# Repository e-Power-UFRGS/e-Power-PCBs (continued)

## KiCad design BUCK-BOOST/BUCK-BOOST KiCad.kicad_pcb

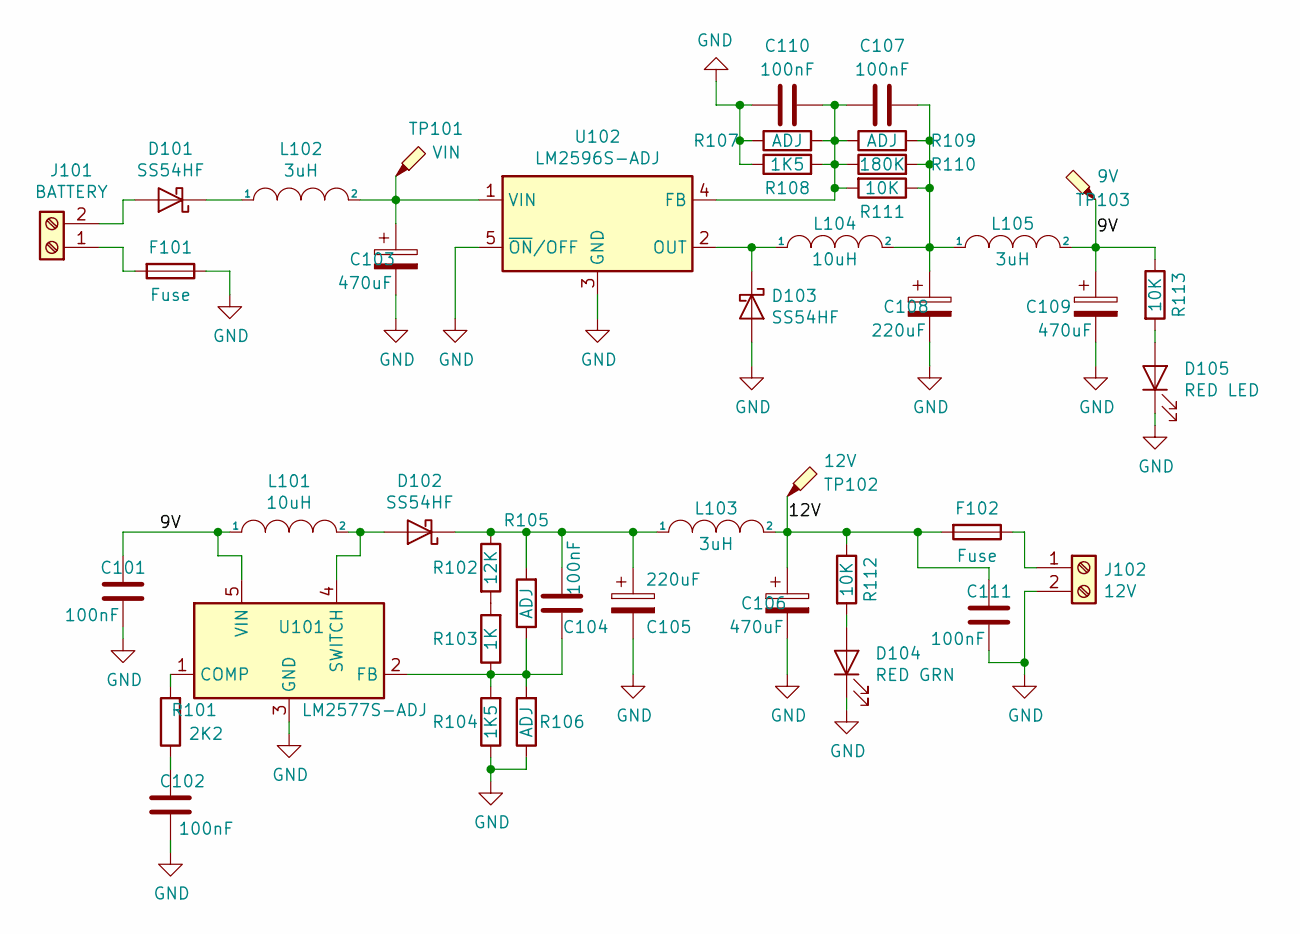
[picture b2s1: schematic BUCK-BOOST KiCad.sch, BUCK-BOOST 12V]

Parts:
C101, C102, C104, C107, C110, C111: 100nF; C_0805_2012Metric
C103, C106, C109: 470uF; CP_Elec_10x10
C105, C108: 220uF; CP_Elec_10x10
D101, D102, D103: SS54HF; DO-214AC
D104: RED GRN; LED_0805_1.15x1.40mm_HandSolder
D105: RED LED; LED_0805_1.15x1.40mm_HandSolder
F101, F102: Fuse; Fuse_SMD
J101: BATTERY; PinHeader_1x02_P2.54mm_Vertical
J102: 12V; PinHeader_1x02_P2.54mm_Vertical
L101, L104: 10uH; L_10.4x10.4_H4.8
L102, L103, L105: 3uH; L_10.4x10.4_H4.8
R101: 2K2; R_0805_2012Metric
R102: 12K; R_0805_2012Metric
R103: 1K; R_0805_2012Metric
R104, R108: 1K5; R_0805_2012Metric
R105, R106, R107, R109: ADJ; R_0805_2012Metric
R110: 180K; R_0805_2012Metric
R111, R112, R113: 10K; R_0805_2012Metric
TP101: VIN; TestPoint_Pad_1.5x1.5mm
TP102: 12V; TestPoint_Pad_1.5x1.5mm
TP103: 9V; TestPoint_Pad_1.5x1.5mm
U101: LM2577S-ADJ; TO-263-5_TabPin3
U102: LM2596S-ADJ; TO-263-5_TabPin3

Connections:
/9V: C101.2, C109.1, L101.1, L105.2, R113.1, TP103.1, U101.5 (VIN)
/12V: C106.1, C111.2, F102.2, L103.2, R112.1, TP102.1
GND: C101.1, C102.1, C103.2, C105.2, C106.2, C108.2, C109.2, C110.2, C111.1, D103.2 (A), D104.1 (K), D105.1 (K), F101.1, J102.2, R104.1, R106.1, R107.1, R108.1, U101.3 (GND), U102.3 (GND), U102.5 (~ON~/OFF)
unnamed: C102.2, R101.1
unnamed: C103.1, L102.2, TP101.1, U102.1 (VIN)
unnamed: C104.1, R103.1, R104.2, R105.1, R106.2, U101.2 (FB)
unnamed: C104.2, C105.1, D102.1 (K), L103.1, R102.1, R105.2
unnamed: C107.1, C108.1, L104.2, L105.1, R109.2, R110.2, R111.1
unnamed: C107.2, C110.1, R107.2, R108.2, R109.1, R110.1, R111.2, U102.4 (FB)
unnamed: D101.1 (K), L102.1
unnamed: D101.2 (A), J101.2
unnamed: D102.2 (A), L101.2, U101.4 (SWITCH)
unnamed: D103.1 (K), L104.1, U102.2 (OUT)
unnamed: D104.2 (A), R112.2
unnamed: D105.2 (A), R113.2
unnamed: F101.2, J101.1
unnamed: F102.1, J102.1
unnamed: R101.2, U101.1 (COMP)
unnamed: R102.2, R103.2

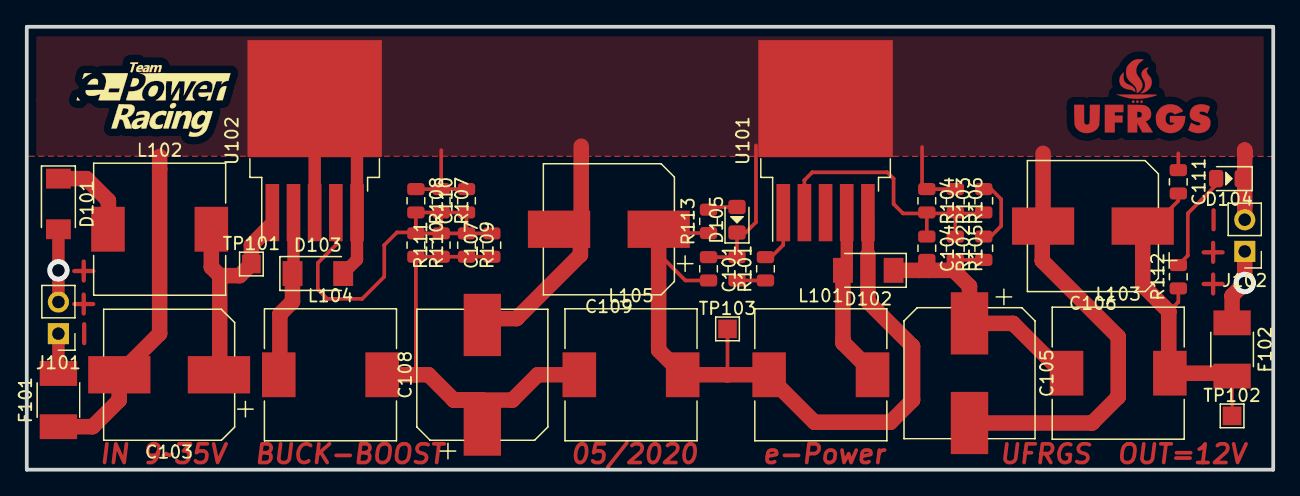
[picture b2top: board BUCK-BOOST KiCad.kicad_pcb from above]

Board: 2 copper layers, 100.1 x 35.6 mm, 43 parts (0 on the bottom side), 19 nets.

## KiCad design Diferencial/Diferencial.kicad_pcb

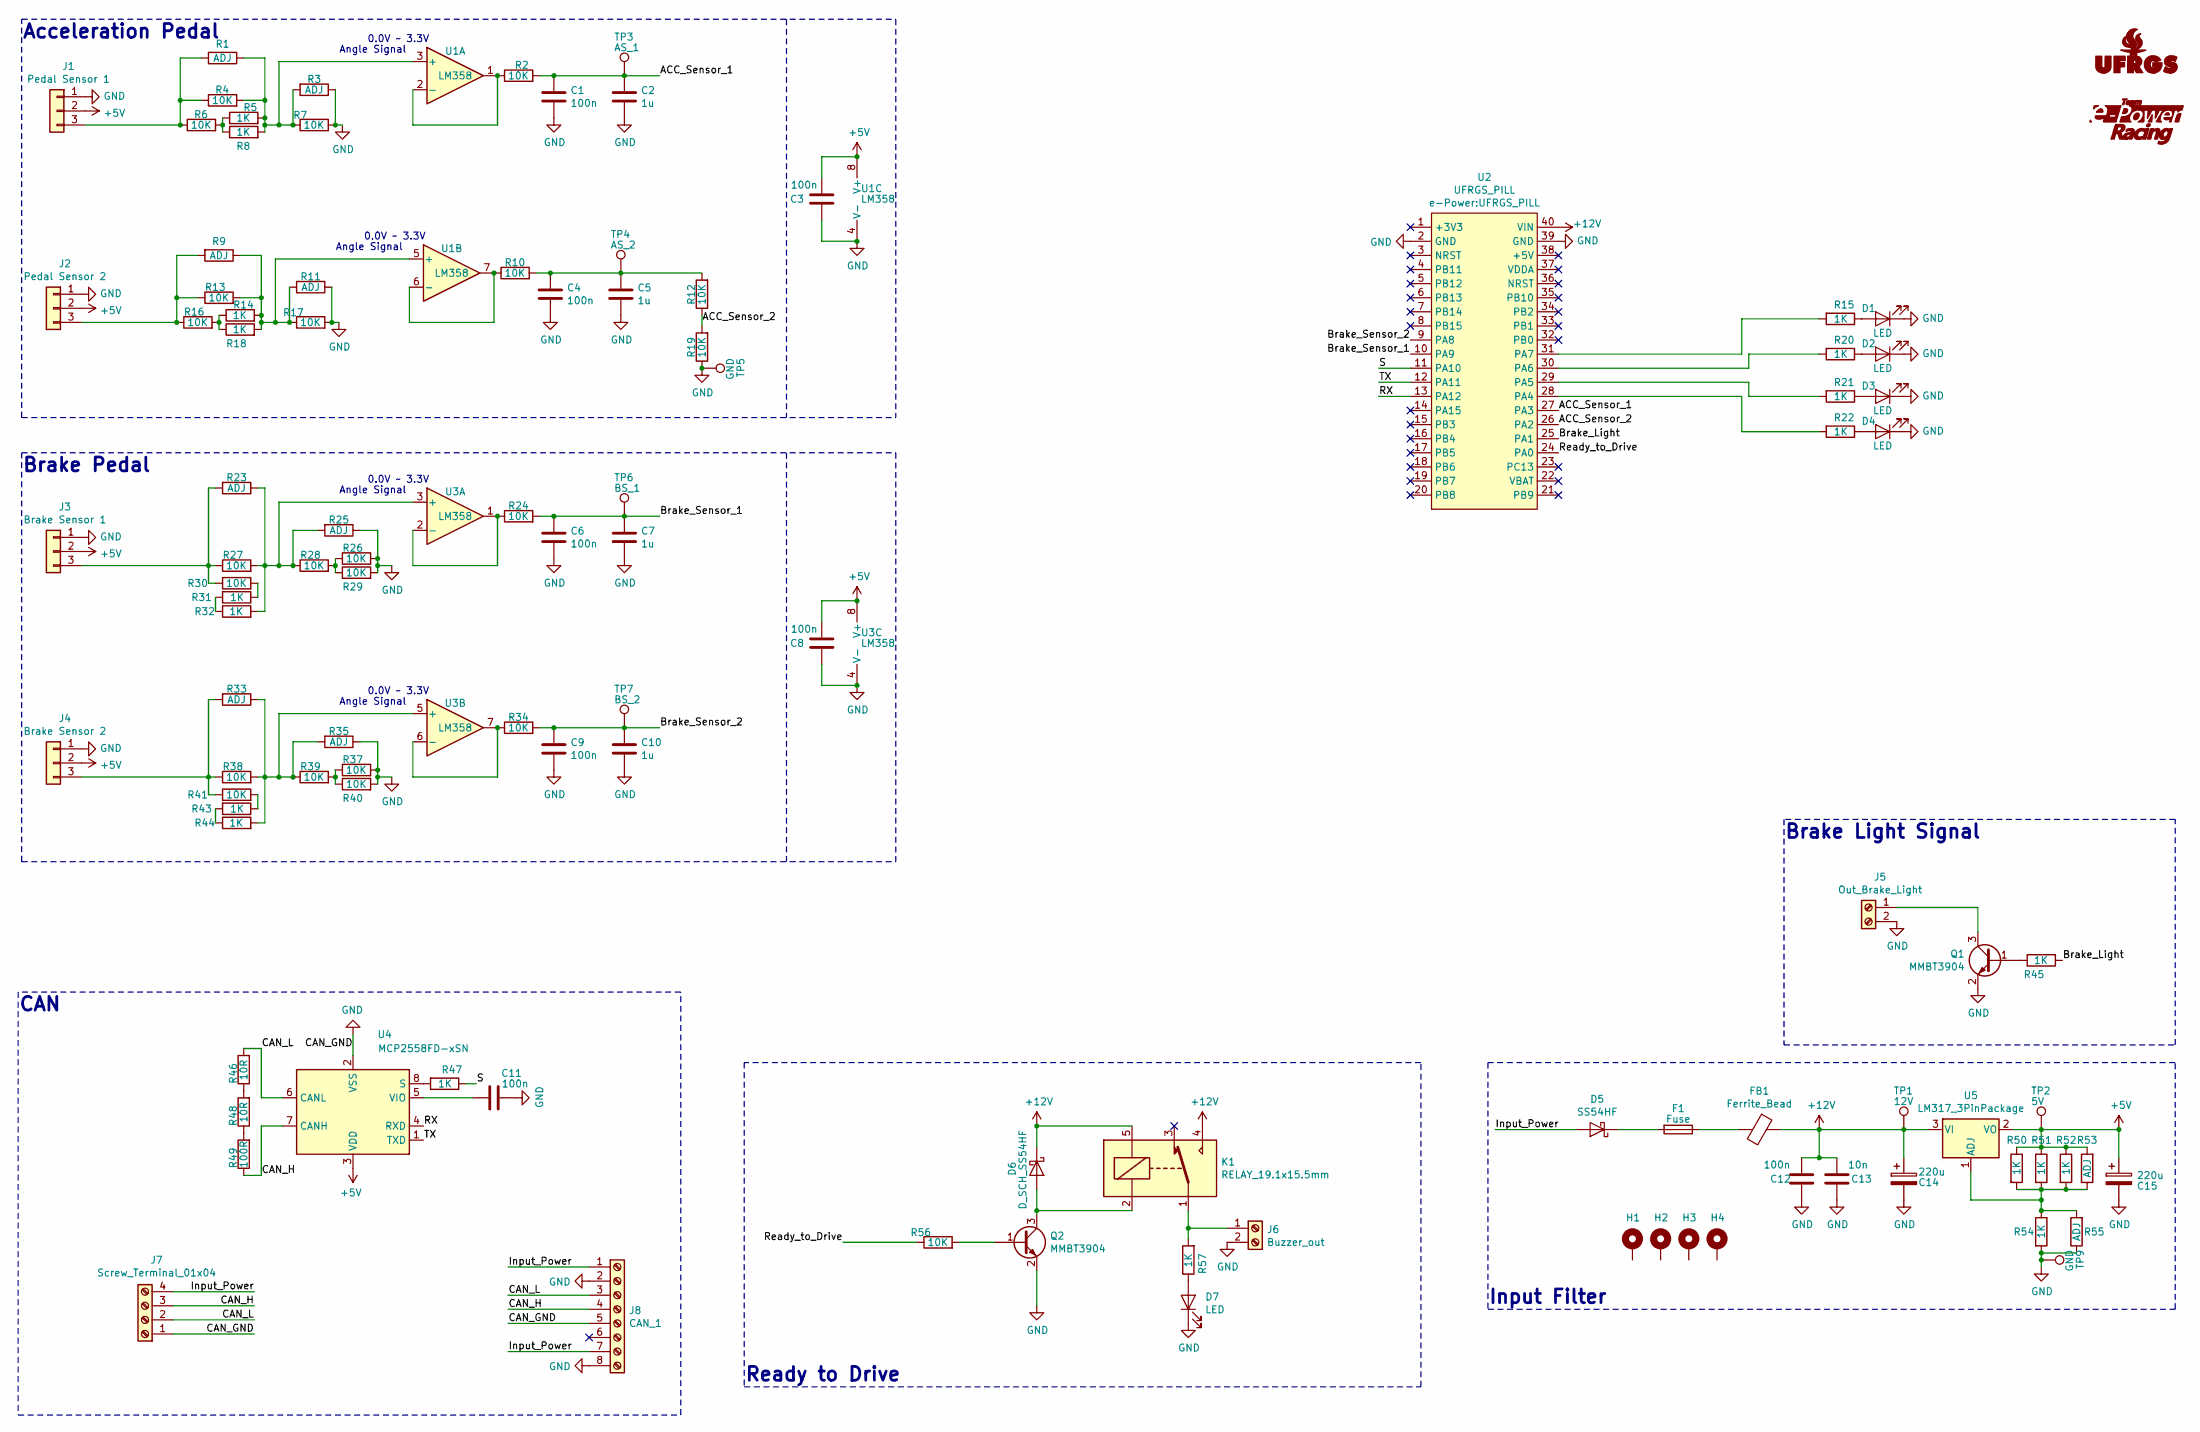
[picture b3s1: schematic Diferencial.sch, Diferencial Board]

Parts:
C1, C3, C4, C6, C8, C9, C11, C12: 100n; C_0805_2012Metric_Pad1.15x1.40mm_HandSolder
C2, C5, C7, C10: 1u; C_0805_2012Metric_Pad1.15x1.40mm_HandSolder
C13: 10n; C_0805_2012Metric_Pad1.15x1.40mm_HandSolder
C14, C15: 220u; CP_Elec_10x10
D1, D2, D3, D4, D7: LED; LED_0805_1.15x1.40mm_HandSolder
D5: SS54HF; DO-214AC
D6: D_SCH_SS54HF; DO-214AC; LCSC C22452
F1: Fuse; FUSE_1206_3216Metric
FB1: Ferrite_Bead; FB_0805_2012Metric
G1: Logo_UFRGS_Large; Logo_UFRGS_14.7x8.0mm_SilkS
G2: Logo_e-Power_Large; Logo_e-Power_16.5x8.0mm_SilkS
H1: +12V; MountingHole_3.2mm_M3_Pad_Via
H2, H3, H4: GND; MountingHole_3.2mm_M3_Pad_Via
J1: Pedal Sensor 1; TerminalBlock_Phoenix_MKDS-1,5-4-5.08_1x04_P5.08mm_Horizont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
J2: Pedal Sensor 2; TerminalBlock_Phoenix_MKDS-1,5-4-5.08_1x04_P5.08mm_Horizont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
J3: Brake Sensor 1; TerminalBlock_Phoenix_MKDS-1,5-4-5.08_1x04_P5.08mm_Horizont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
J4: Brake Sensor 2; TerminalBlock_Phoenix_MKDS-1,5-4-5.08_1x04_P5.08mm_Horizont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
J5: Out_Brake_Light; TerminalBlock_Phoenix_MKDS-1,5-2_1x02_P5.08mm_Horizontal
J6: Buzzer_out; TerminalBlock_Phoenix_MKDS-1,5-2_1x02_P5.08mm_Horizontal
J7: Screw_Terminal_01x04; TerminalBlock_Phoenix_MKDS-1,5-4-5.08_1x04_P5.08mm_Horizont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
J8: CAN_1; Molex_Mini-Fit_Jr_2x04_P4.20mm_Horizontal
K1: RELAY_19.1x15.5mm; Relay_SPDT_SANYOU_SRD
Q1, Q2: MMBT3904; SOT-23
R1, R3, R9, R11, R23, R25, R33, R35, R53, R55: ADJ; R_0805_2012Metric_Pad1.15x1.40mm_HandSolder
R2, R4, R6, R7, R10, R12, R13, R16, R17, R19, R24, R26, R27, R28, R29, R30, R34, R37, R38, R39, R40, R41, R56: 10K; R_0805_2012Metric_Pad1.15x1.40mm_HandSolder
R5, R8, R14, R15, R18, R20, R21, R22, R31, R32, R43, R44, R45, R47, R50, R51, R52, R54, R57: 1K; R_0805_2012Metric_Pad1.15x1.40mm_HandSolder
R46, R48: 10R; R_0805_2012Metric_Pad1.15x1.40mm_HandSolder
R49: 100R; R_0805_2012Metric_Pad1.15x1.40mm_HandSolder
TP1: 12V; TestPoint_Pad_D1.0mm
TP2: 5V; TestPoint_Pad_D1.0mm
TP3: AS_1; TestPoint_Pad_D1.0mm
TP4: AS_2; TestPoint_Pad_D1.0mm
TP5, TP9: GND; TestPoint_Pad_D1.0mm
TP6: BS_1; TestPoint_Pad_D1.0mm
TP7: BS_2; TestPoint_Pad_D1.0mm
U1, U3: LM358; SOIC-8_3.9x4.9mm_P1.27mm
U2: UFRGS_PILL
U4: MCP2558FD-xSN; SOIC-8_3.9x4.9mm_P1.27mm
U5: LM317_3PinPackage; TO-220-3_Horizontal_TabDown

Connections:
+5V: C3.1, C8.1, C15.1, J1.2, J2.2, J3.2, J4.2, R50.1, R51.1, R52.1, R53.2, TP2.1, U1.8 (V+), U3.8 (V+), U4.3 (VDD), U5.2 (VO)
+12V: C12.1, C13.1, C14.1, D6.1 (K), FB1.1, K1.4, K1.5, TP1.1, U2.40 (VIN), U5.3 (VI)
/ACC_Sensor_1: C1.2, C2.2, R2.2, TP3.1, U2.27 (PA3)
/ACC_Sensor_2: R12.1, R19.2, U2.26 (PA2)
/Brake_Light: R45.2, U2.25 (PA1)
/Brake_Sensor_1: C6.2, C7.2, R24.2, TP6.1, U2.10 (PA9)
/Brake_Sensor_2: C9.2, C10.2, R34.2, TP7.1, U2.9 (PA8)
/CAN_H: J7.3, J8.4, R49.1, U4.7 (CANH)
/CAN_L: J7.2, J8.3, R46.2, U4.6 (CANL)
/Input_Power: D5.2 (A), J7.4, J8.1, J8.7
/RX: U2.13 (PA12), U4.4 (RXD)
/Ready_to_Drive: R56.1, U2.24 (PA0)
/S: R47.1, U2.11 (PA10)
/TX: U2.12 (PA11), U4.1 (TXD)
GND: C1.1, C2.1, C3.2, C4.1, C5.1, C6.1, C7.1, C8.2, C9.1, C10.1, C11.2, C12.2, C13.2, C14.2, C15.2, D1.1 (K), D2.1 (K), D3.1 (K), D4.1 (K), D7.1 (K), J1.1, J2.1, J3.1, J4.1, J5.2, J6.2, J7.1, J8.2, J8.5, J8.8, Q1.2 (E), Q2.2 (E), R3.1, R7.2, R11.1, R17.2, R19.1, R25.1, R26.2, R29.2, R35.1, R37.2, R40.2, R54.2, R55.1, TP5.1, TP9.1, U1.4 (V-), U2.2 (GND), U2.39 (GND), U3.4 (V-), U4.2 (VSS); also elsewhere on the board
unnamed: C4.2, C5.2, R10.2, R12.2, TP4.1
unnamed: C11.1, U4.5 (VIO)
unnamed 17: D1.2 (A), R15.1; also elsewhere on the board
unnamed 18: D2.2 (A), R20.1; also elsewhere on the board
unnamed 19: D3.2 (A), R21.1; also elsewhere on the board
unnamed 20: D4.2 (A), R22.1; also elsewhere on the board
unnamed: D5.1 (K), F1.2
unnamed: D6.2 (A), K1.2, Q2.3 (C)
unnamed: D7.2 (A), R57.1
unnamed: F1.1, FB1.2
unnamed: J1.3, R1.2, R4.1, R6.1
unnamed: J2.3, R9.2, R13.1, R16.1
unnamed: J3.3, R23.2, R27.1, R30.1
unnamed: J4.3, R33.2, R38.1, R41.1
unnamed: J5.1, Q1.3 (C)
unnamed: J6.1, K1.1, R57.2
unnamed: Q1.1 (B), R45.1
unnamed: Q2.1 (B), R56.2
unnamed: R1.1, R3.2, R4.2, R5.2, R7.1, R8.2, U1.3 (+)
unnamed: R2.1, U1.1, U1.2 (-)
unnamed: R5.1, R6.2, R8.1
unnamed: R10.1, U1.6 (-), U1.7
unnamed: R9.1, R11.2, R13.2, R14.2, R17.1, R18.2, U1.5 (+)
unnamed: R14.1, R16.2, R18.1
unnamed: R15.2, U2.31 (PA7)
unnamed: R20.2, U2.30 (PA6)
unnamed: R21.2, U2.29 (PA5)
unnamed: R22.2, U2.28 (PA4)
unnamed: R23.1, R25.2, R27.2, R28.1, R32.2, U3.3 (+)
unnamed: R24.1, U3.1, U3.2 (-)
unnamed: R26.1, R28.2, R29.1
unnamed: R30.2, R31.1
unnamed: R31.2, R32.1
unnamed: R33.1, R35.2, R38.2, R39.1, R44.2, U3.5 (+)
unnamed: R34.1, U3.6 (-), U3.7
unnamed: R37.1, R39.2, R40.1
unnamed: R41.2, R43.1
unnamed: R43.2, R44.1
unnamed: R46.1, R48.2
unnamed: R47.2, U4.8 (S)
unnamed: R48.1, R49.2
unnamed: R50.2, R51.2, R52.2, R53.1, R54.1, R55.2, U5.1 (ADJ)

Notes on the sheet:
Angle Signal
0.0V ~~ 3.3V
Acceleration Pedal
Brake Pedal
CAN
Input Filter
Ready to Drive
Brake Light Signal

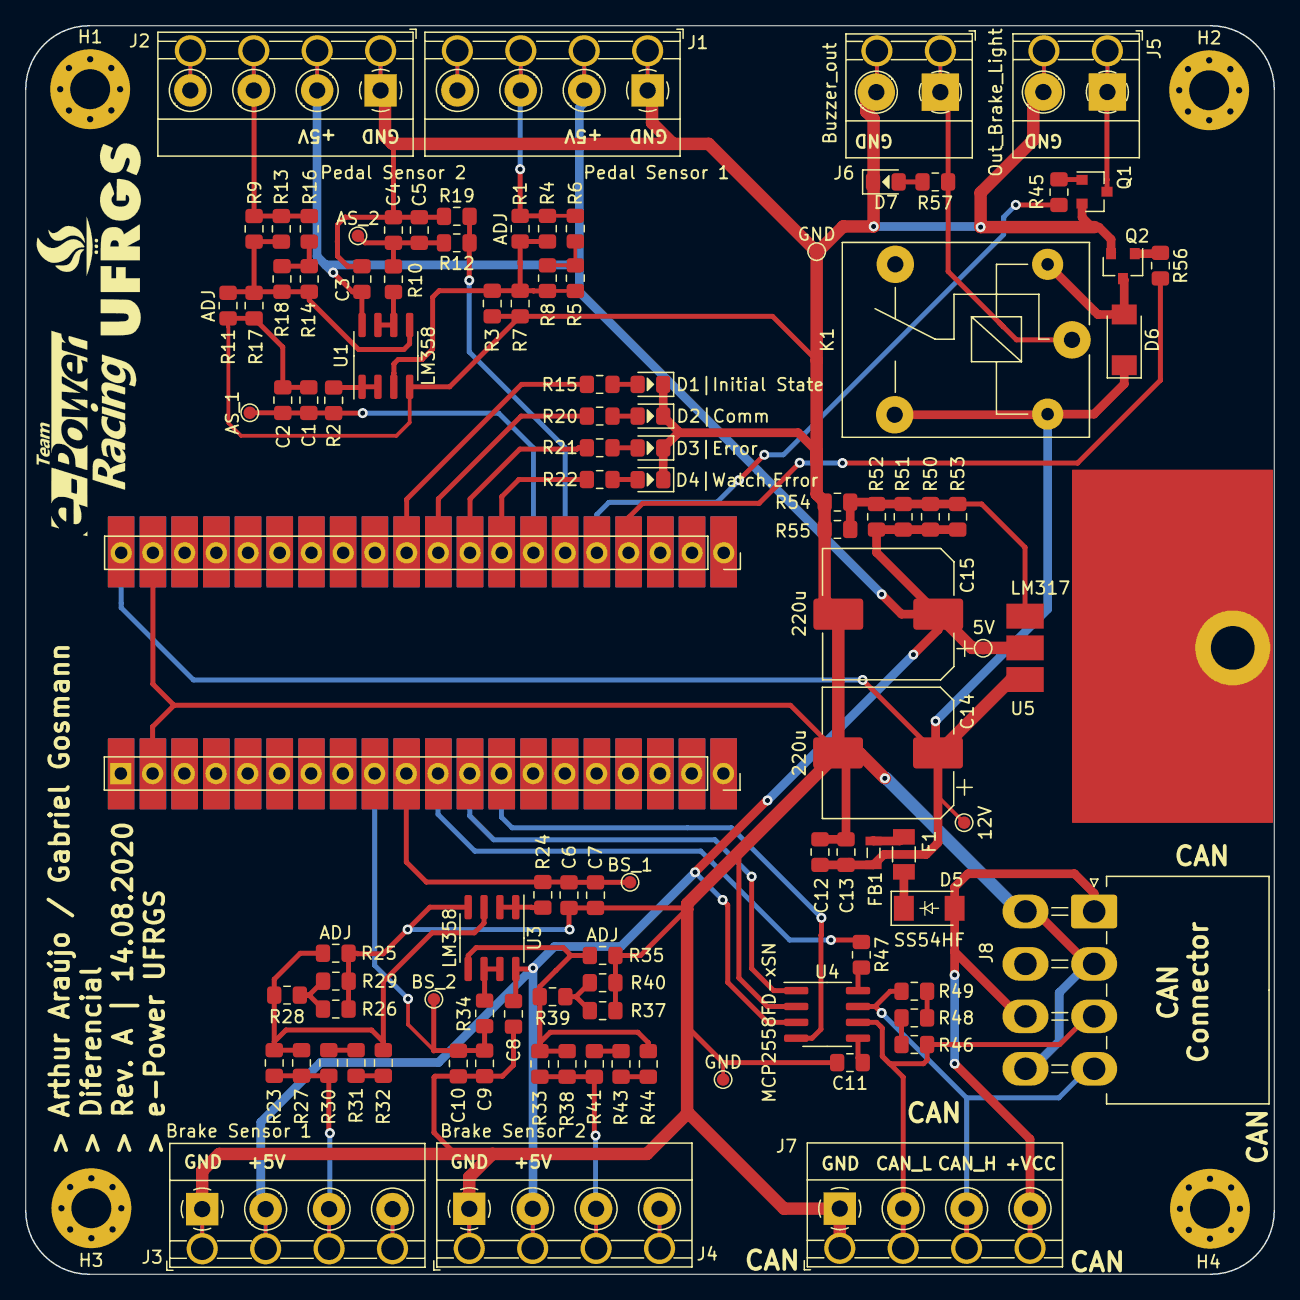
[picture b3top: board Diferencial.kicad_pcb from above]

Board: 2 copper layers, 100.0 x 100.0 mm, 109 parts (0 on the bottom side), 57 nets.

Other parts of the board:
D1|Initial State, D2|Comm, D3|Error, D4|Watch.Error: LED; LED_0805_1.15x1.40mm_HandSolder

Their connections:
GND: D1|Initial State.1, D2|Comm.1, D3|Error.1, D4|Watch.Error.1; also elsewhere on the board
unnamed 17: D1|Initial State.2; also elsewhere on the board
unnamed 18: D2|Comm.2; also elsewhere on the board
unnamed 19: D3|Error.2; also elsewhere on the board
unnamed 20: D4|Watch.Error.2; also elsewhere on the board

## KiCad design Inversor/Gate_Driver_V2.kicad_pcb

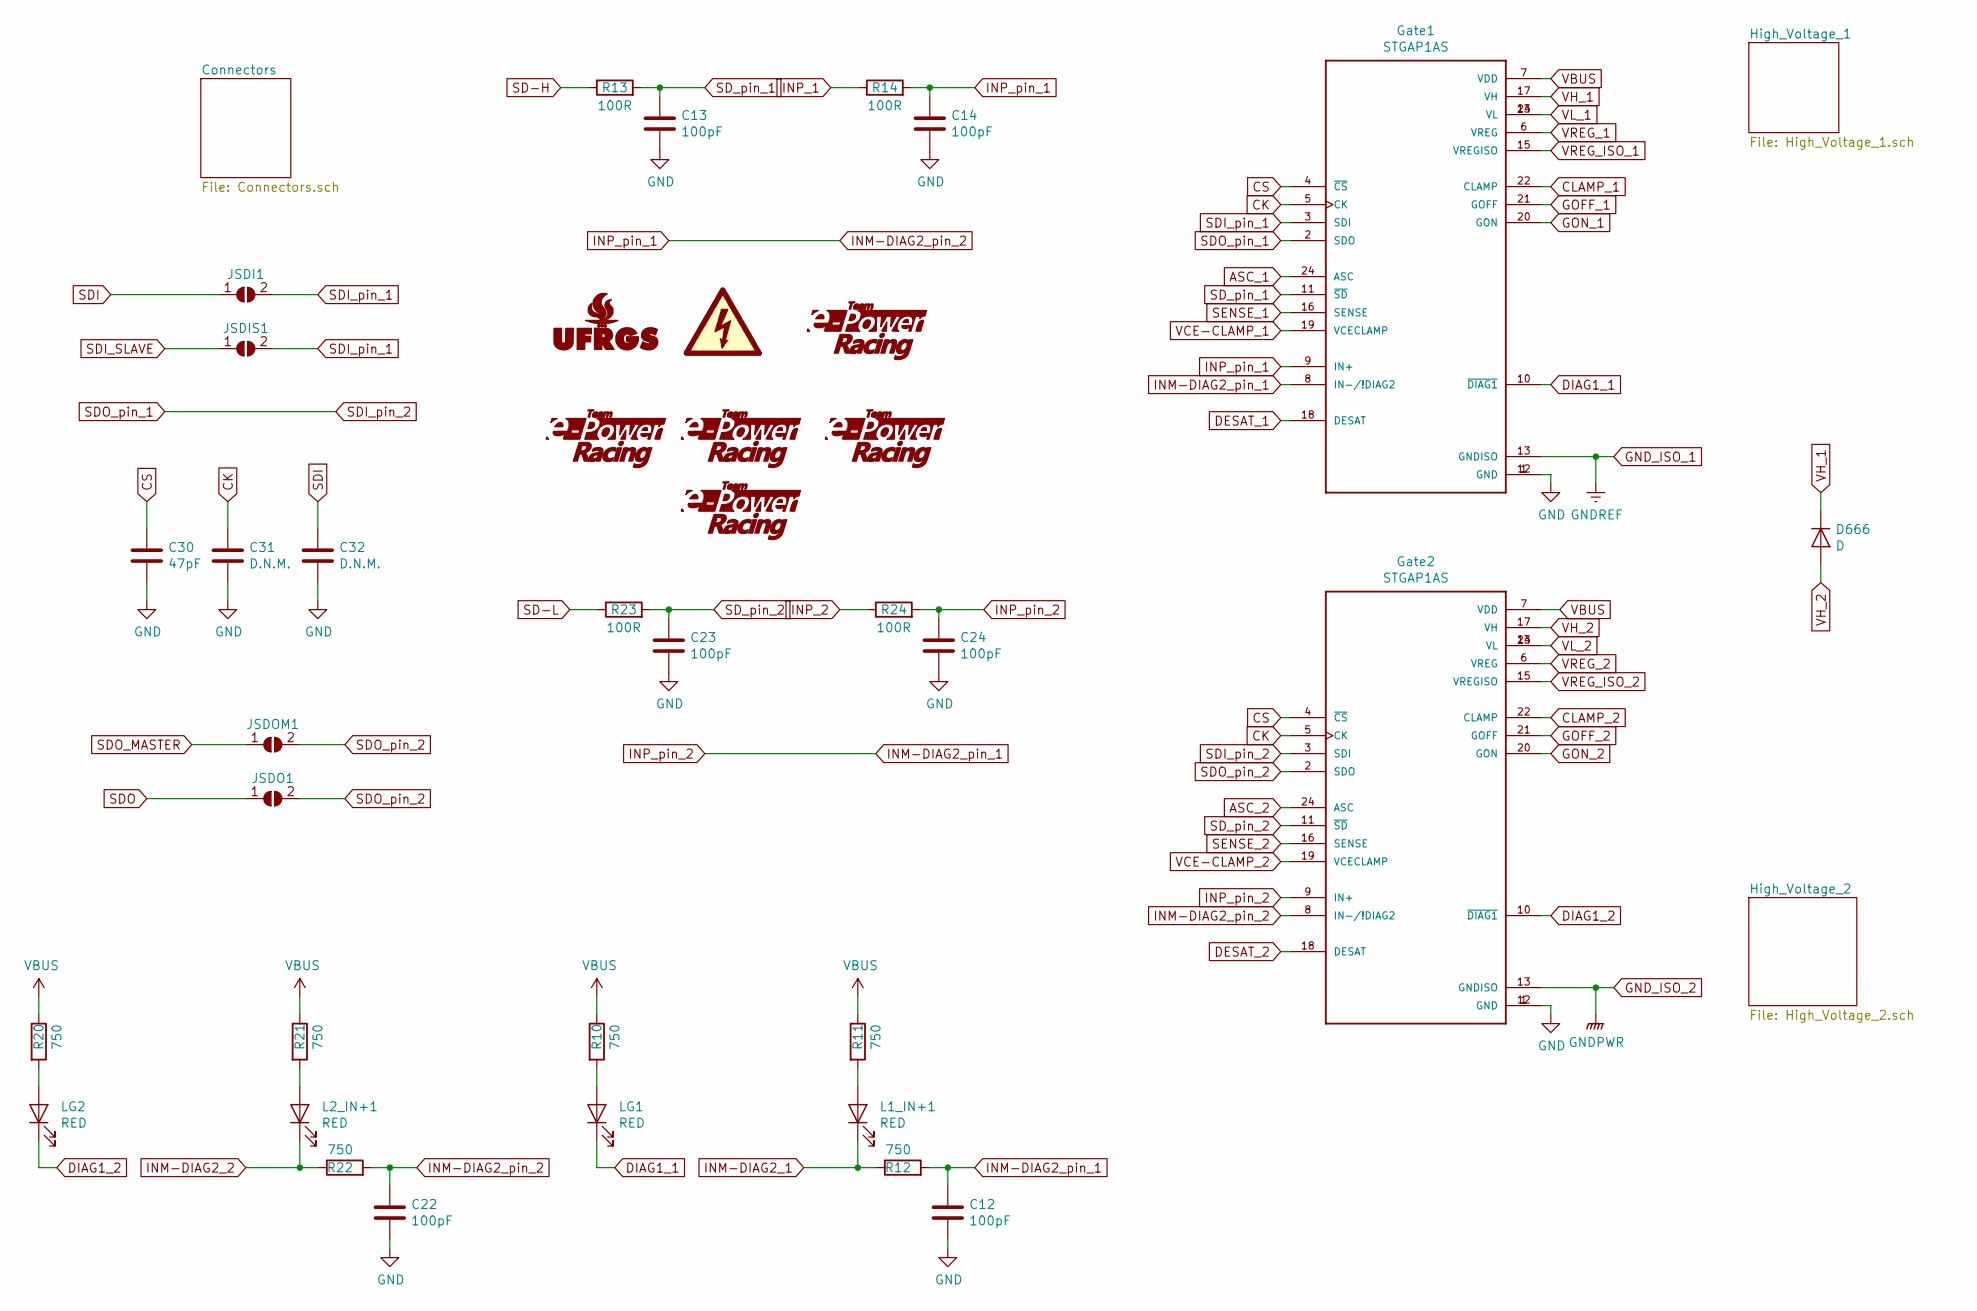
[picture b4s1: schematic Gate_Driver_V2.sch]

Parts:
C12, C13, C14, C22, C23, C24: 100pF; C_0805_2012Metric
C30: 47pF; C_0805_2012Metric
C31, C32: D.N.M.; C_0805_2012Metric
D666: D; DO-214AC
G1: Logo_UFRGS_Large; Logo_UFRGS_11.0x6.0mm_SilkS
G2: High_Voltage; Logo_High_Voltage_9.1x8.0mm_SilkS
G3: Logo_e-Power_Large; Logo_e-Power_12.4x6.0mm_SilkS
G4, G5, G6, G7: Logo_e-Power_Large; MountingHole_3.2mm_M3
Gate1, Gate2: STGAP1AS; SOP-24_7.5x15.4mm_P1.27mm
JSDI1: SolderJumper_2_Open; PinHeader_1x02_P2.54mm_Vertical
JSDIS1: SolderJumper_2_Open; PinHeader_1x02_P2.54mm_Vertical
JSDO1: SolderJumper_2_Open; PinHeader_1x02_P2.54mm_Vertical
JSDOM1: SolderJumper_2_Open; PinHeader_1x02_P2.54mm_Vertical
L1_IN+1, L2_IN+1: RED; LED_0805_2012Metric
LG1, LG2: RED; LED_0805_2012Metric
R10, R11, R12, R20, R21, R22: 750; R_0805_2012Metric
R13, R14, R23, R24: 100R; R_0805_2012Metric

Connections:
ASC_1: Gate1.24 (ASC); also elsewhere on the board
ASC_2: Gate2.24 (ASC); also elsewhere on the board
CK: C31.1, Gate1.5 (CK), Gate2.5 (CK); also elsewhere on the board
CS: C30.1, Gate1.4 (~CS~), Gate2.4 (~CS~); also elsewhere on the board
DESAT_1: Gate1.18 (DESAT); also elsewhere on the board
DESAT_2: Gate2.18 (DESAT); also elsewhere on the board
DIAG1_1: Gate1.10 (~DIAG1~), LG1.1 (K); also elsewhere on the board
DIAG1_2: Gate2.10 (~DIAG1~), LG2.1 (K); also elsewhere on the board
GND: C12.2, C13.2, C14.2, C22.2, C23.2, C24.2, C30.2, C31.2, C32.2, Gate1.1 (GND), Gate1.12 (GND), Gate2.1 (GND), Gate2.12 (GND); also elsewhere on the board
GND_ISO_2: Gate2.13 (GNDISO); also elsewhere on the board
GOFF_1: Gate1.21 (GOFF); also elsewhere on the board
GOFF_2: Gate2.21 (GOFF); also elsewhere on the board
GON_1: Gate1.20 (GON); also elsewhere on the board
GON_2: Gate2.20 (GON); also elsewhere on the board
INM-DIAG2_1: L1_IN+1.1 (K), R12.1
INM-DIAG2_2: L2_IN+1.1 (K), R22.1
INM-DIAG2_pin_1: C12.1, C24.1, Gate1.8 (IN-/!DIAG2), Gate2.9 (IN+), R12.2, R24.2; also elsewhere on the board
INM-DIAG2_pin_2: C14.1, C22.1, Gate1.9 (IN+), Gate2.8 (IN-/!DIAG2), R14.2, R22.2; also elsewhere on the board
INP_1: R14.1; also elsewhere on the board
INP_2: R24.1; also elsewhere on the board
unnamed: L1_IN+1.2 (A), R11.2
unnamed: L2_IN+1.2 (A), R21.2
unnamed: LG1.2 (A), R10.2
unnamed: LG2.2 (A), R20.2
SD-H: R13.1; also elsewhere on the board
SD-L: R23.1; also elsewhere on the board
SDI: C32.1, JSDI1.1 (A); also elsewhere on the board
SDI_SLAVE: JSDIS1.1 (A); also elsewhere on the board
SDI_pin_1: Gate1.3 (SDI), JSDI1.2 (B), JSDIS1.2 (B)
SDI_pin_2: Gate1.2 (SDO), Gate2.3 (SDI)
SDO: JSDO1.1 (A); also elsewhere on the board
SDO_MASTER: JSDOM1.1 (A); also elsewhere on the board
SDO_pin_2: Gate2.2 (SDO), JSDO1.2 (B), JSDOM1.2 (B)
SD_pin_1: C13.1, Gate1.11 (~SD~), R13.2; also elsewhere on the board
SD_pin_2: C23.1, Gate2.11 (~SD~), R23.2; also elsewhere on the board
SENSE_1: Gate1.16 (SENSE); also elsewhere on the board
SENSE_2: Gate2.16 (SENSE); also elsewhere on the board
VBUS: Gate1.7 (VDD), Gate2.7 (VDD), R10.1, R11.1, R20.1, R21.1; also elsewhere on the board
VCE-CLAMP_1: Gate1.19 (VCECLAMP); also elsewhere on the board
VCE-CLAMP_2: Gate2.19 (VCECLAMP); also elsewhere on the board
VH_1: D666.1 (K), Gate1.17 (VH); also elsewhere on the board
VH_2: D666.2 (A), Gate2.17 (VH); also elsewhere on the board
VL_1: Gate1.14 (VL), Gate1.23 (VL); also elsewhere on the board
VL_2: Gate2.14 (VL), Gate2.23 (VL); also elsewhere on the board
VREG_1: Gate1.6 (VREG); also elsewhere on the board
VREG_2: Gate2.6 (VREG); also elsewhere on the board
VREG_ISO_1: Gate1.15 (VREGISO); also elsewhere on the board
VREG_ISO_2: Gate2.15 (VREGISO); also elsewhere on the board

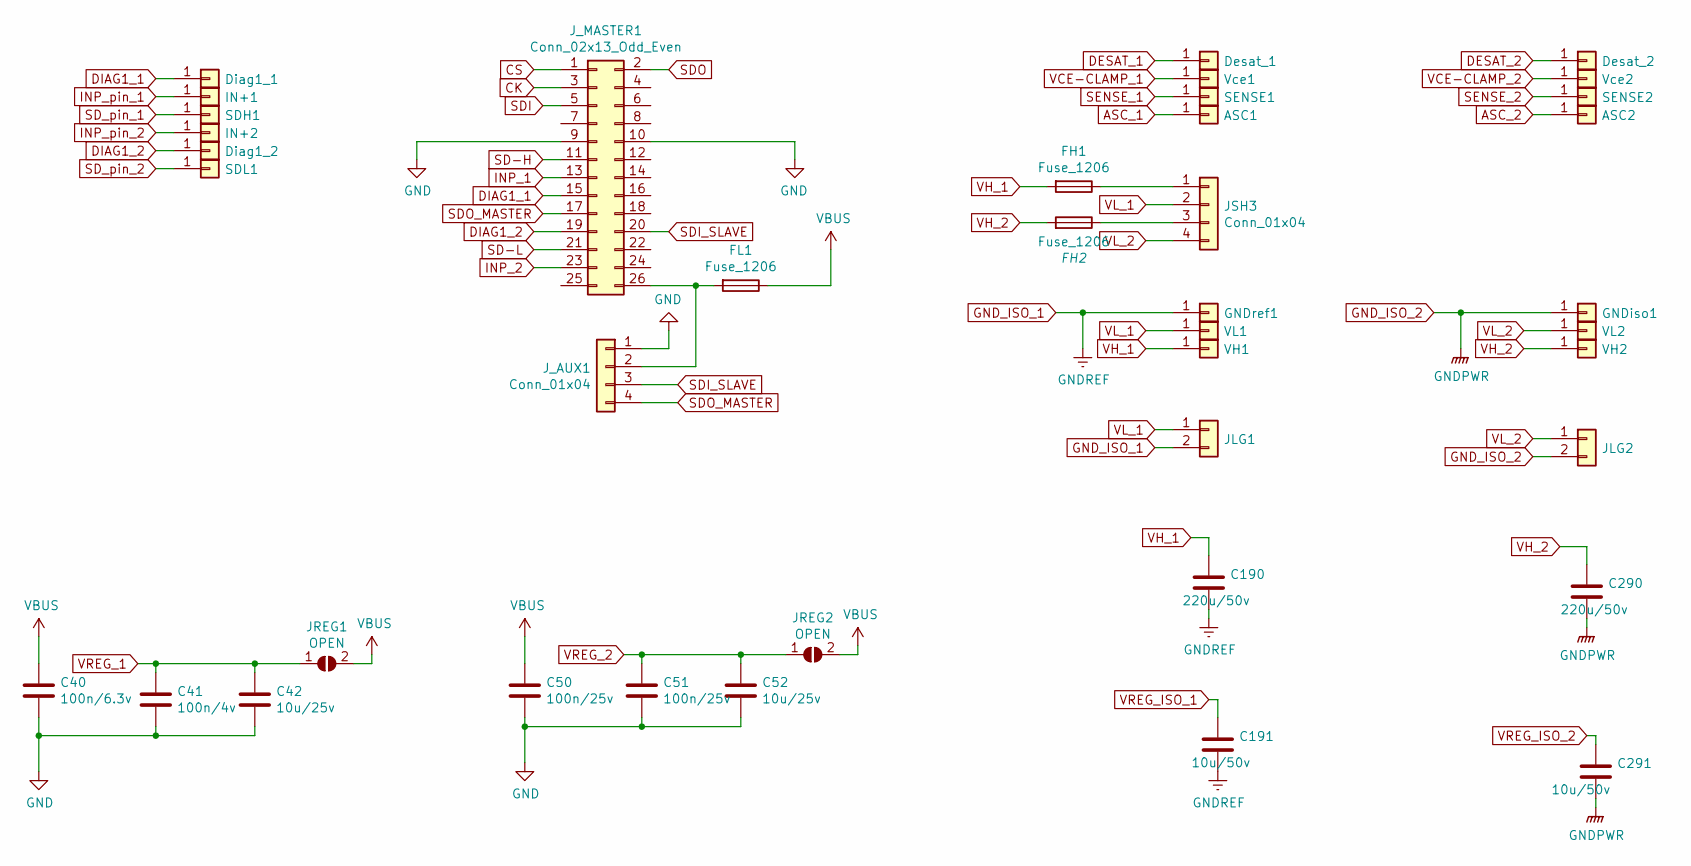
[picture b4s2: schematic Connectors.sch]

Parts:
ASC1, ASC2: Conn_01x01; TestPoint_Pad_D1.5mm
C40: 100n/6.3v; C_0805_2012Metric
C41: 100n/4v; C_0805_2012Metric
C42, C52: 10u/25v; C_0805_2012Metric
C50, C51: 100n/25v; C_0805_2012Metric
C190, C290: 220u/50v; CP_Elec_8x10
C191, C291: 10u/50v; C_0805_2012Metric
Desat_1, Desat_2: Conn_01x01; TestPoint_Pad_D1.5mm
Diag1_1, Diag1_2: Conn_01x01; TestPoint_Pad_D1.5mm
FH1, FH2: Fuse_1206; FUSE_1206_3216Metric
FL1: Fuse_1206; FUSE_1206_3216Metric
GNDiso1: Conn_01x01; TestPoint_Pad_D1.5mm
GNDref1: Conn_01x01; TestPoint_Pad_D1.5mm
IN+1, IN+2: Conn_01x01; TestPoint_Pad_D1.5mm
JLG1, JLG2: Conn_01x02; PinHeader_1x02_P2.54mm_Vertical
JREG1, JREG2: OPEN; PinHeader_1x02_P2.54mm_Vertical
JSH3: Conn_01x04; PinSocket_2x02_P2.54mm_Vertical
J_AUX1: Conn_01x04; PinSocket_2x02_P2.54mm_Vertical
J_MASTER1: Conn_02x13_Odd_Even; PinSocket_2x13_P2.54mm_Vertical
SDH1: Conn_01x01; TestPoint_Pad_1.5x1.5mm
SDL1: Conn_01x01; TestPoint_Pad_1.5x1.5mm
SENSE1, SENSE2: Conn_01x01; TestPoint_Pad_1.5x1.5mm
VH1, VH2: Conn_01x01; TestPoint_Pad_D1.5mm
VL1, VL2: Conn_01x01; TestPoint_Pad_D1.5mm
Vce1, Vce2: Conn_01x01; TestPoint_Pad_1.5x1.5mm

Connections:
ASC_1: ASC1.1; also elsewhere on the board
ASC_2: ASC2.1; also elsewhere on the board
CK: J_MASTER1.3; also elsewhere on the board
CS: J_MASTER1.1; also elsewhere on the board
DESAT_1: Desat_1.1; also elsewhere on the board
DESAT_2: Desat_2.1; also elsewhere on the board
DIAG1_1: Diag1_1.1, J_MASTER1.15; also elsewhere on the board
DIAG1_2: Diag1_2.1, J_MASTER1.19; also elsewhere on the board
GND: C40.2, C41.2, C42.2, C50.2, C51.2, C52.2, J_AUX1.1, J_MASTER1.9, J_MASTER1.10; also elsewhere on the board
GND_ISO_2: C290.2, C291.2, GNDiso1.1, JLG2.2; also elsewhere on the board
INM-DIAG2_pin_1: IN+2.1; also elsewhere on the board
INM-DIAG2_pin_2: IN+1.1; also elsewhere on the board
INP_1: J_MASTER1.13; also elsewhere on the board
INP_2: J_MASTER1.23; also elsewhere on the board
unnamed: FH1.1, JSH3.1
unnamed: FH2.1, JSH3.3
unnamed: FL1.2, J_AUX1.2, J_MASTER1.26
SD-H: J_MASTER1.11; also elsewhere on the board
SD-L: J_MASTER1.21; also elsewhere on the board
SDI: J_MASTER1.5; also elsewhere on the board
SDI_SLAVE: J_AUX1.3, J_MASTER1.20; also elsewhere on the board
SDO: J_MASTER1.2; also elsewhere on the board
SDO_MASTER: J_AUX1.4, J_MASTER1.17; also elsewhere on the board
SD_pin_1: SDH1.1; also elsewhere on the board
SD_pin_2: SDL1.1; also elsewhere on the board
SENSE_1: SENSE1.1; also elsewhere on the board
SENSE_2: SENSE2.1; also elsewhere on the board
VBUS: C40.1, C50.1, FL1.1, JREG1.2 (B), JREG2.2 (B); also elsewhere on the board
VCE-CLAMP_1: Vce1.1; also elsewhere on the board
VCE-CLAMP_2: Vce2.1; also elsewhere on the board
VH_1: C190.1, FH1.2, VH1.1; also elsewhere on the board
VH_2: C290.1, FH2.2, VH2.1; also elsewhere on the board
VL_1: JLG1.1, JSH3.2, VL1.1; also elsewhere on the board
VL_2: JLG2.1, JSH3.4, VL2.1; also elsewhere on the board
VREG_1: C41.1, C42.1, JREG1.1 (A); also elsewhere on the board
VREG_2: C51.1, C52.1, JREG2.1 (A); also elsewhere on the board
VREG_ISO_1: C191.1; also elsewhere on the board
VREG_ISO_2: C291.1; also elsewhere on the board

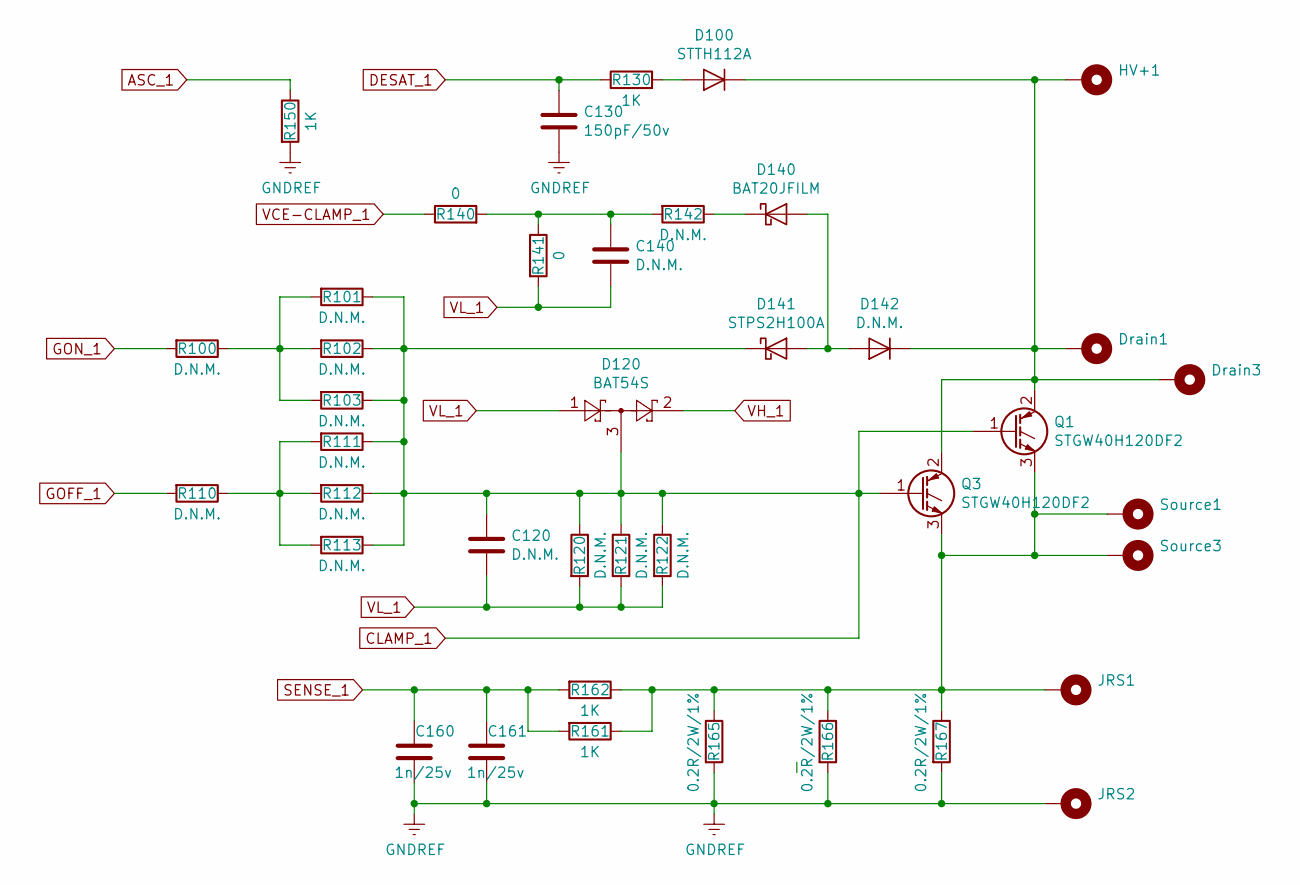
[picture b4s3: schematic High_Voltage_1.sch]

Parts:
C120, C140: D.N.M.; C_0805_2012Metric
C130: 150pF/50v; C_0805_2012Metric
C160, C161: 1n/25v; C_0805_2012Metric
D100: STTH112A; D_SMA
D120: BAT54S; SOT-23
D140: BAT20JFILM; DO-214AC
D141: STPS2H100A; DO-214AC
D142: D.N.M.; D_SMA
Drain1, Drain3: MountingHole_Pad; MountingHole_2.2mm_M2_DIN965_Pad
HV+1: MountingHole_Pad; MountingHole_4.5mm_Pad
JRS1, JRS2: MountingHole_Pad; MountingHole_2.2mm_M2_DIN965_Pad
Q1, Q3: STGW40H120DF2; TO-247-3_Vertical
R100, R101, R102, R103, R110, R111, R112, R113, R120, R121, R122, R142: D.N.M.; R_0805_2012Metric
R130, R150, R161, R162: 1K; R_0805_2012Metric
R140, R141: 0; R_0805_2012Metric
R165, R166, R167: 0.2R/2W/1%; R_2512_6332Metric
Source1, Source3: MountingHole_Pad; MountingHole_2.2mm_M2_DIN965_Pad

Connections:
ASC_1: R150.1; also elsewhere on the board
DESAT_1: C130.1, R130.1; also elsewhere on the board
GOFF_1: R110.2; also elsewhere on the board
GON_1: R100.2; also elsewhere on the board
unnamed: C140.1, R140.2, R141.1, R142.2
unnamed: D140.1 (K), R142.1
unnamed: D140.2 (A), D141.2 (A), D142.2 (A)
unnamed 24: D100.2 (A), R130.2; also elsewhere on the board
unnamed: R100.1, R101.2, R102.2, R103.2
unnamed: R110.1, R111.2, R112.2, R113.2
SENSE_1: C160.1, C161.1, R161.2, R162.2; also elsewhere on the board
VCE-CLAMP_1: R140.1; also elsewhere on the board
VH_1: D120.2; also elsewhere on the board
VL_1: C120.2, C140.2, D120.1, R120.2, R121.2, R122.2, R141.2; also elsewhere on the board
